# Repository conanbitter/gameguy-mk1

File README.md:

# GameGuy mk1
Simple portable game console. Based on ATMega328P.

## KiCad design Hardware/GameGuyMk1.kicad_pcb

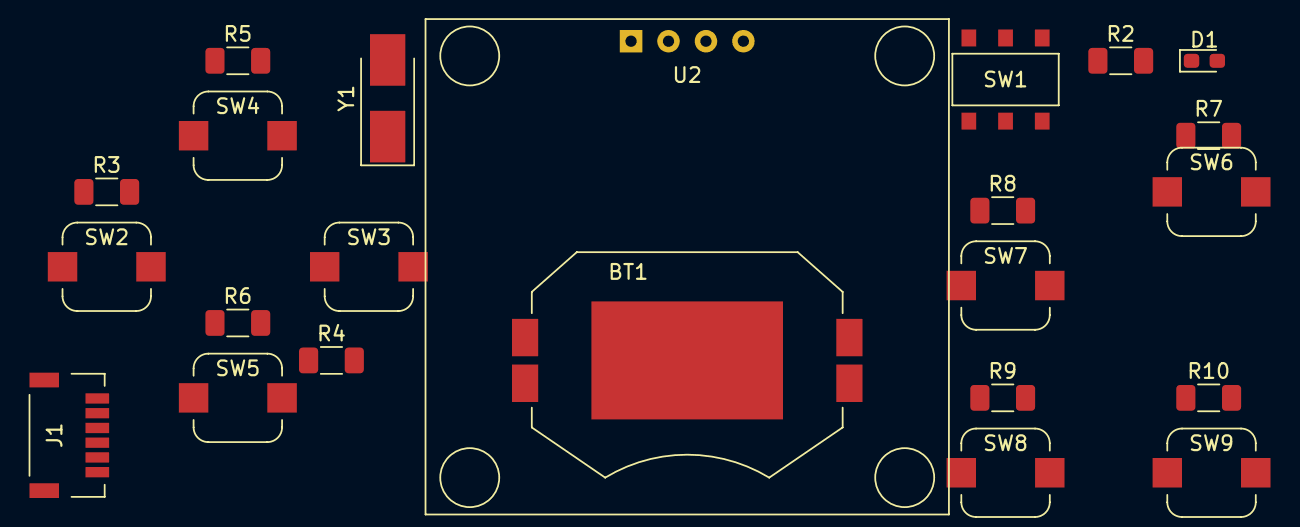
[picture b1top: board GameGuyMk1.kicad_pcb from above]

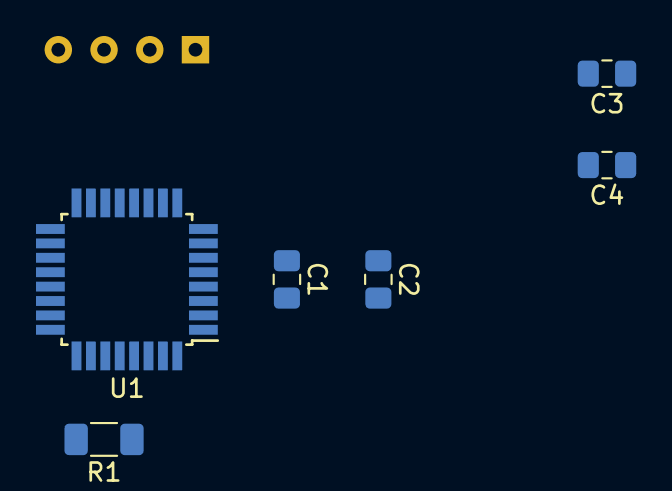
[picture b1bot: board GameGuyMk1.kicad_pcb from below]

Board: 2 copper layers, 29 parts (6 on the bottom side), 21 nets, no tracks yet.

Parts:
BT1: 3V; Battery_Holder
C1, C2: 0.1uF; C_0805_2012Metric_Pad1.18x1.45mm_HandSolder
C3, C4: 22pF; C_0805_2012Metric_Pad1.18x1.45mm_HandSolder
D1: LED; LED_0603_1608Metric_Pad1.05x0.95mm_HandSolder
J1: AVR-ISP-6; Connector_JST1.0_6pin
R1, R3, R4, R5, R6, R7, R8, R9, R10: 10k; R_1206_3216Metric_Pad1.30x1.75mm_HandSolder
R2: 330; R_1206_3216Metric_Pad1.30x1.75mm_HandSolder
SW1: POWER; AYZ0202
SW2: Left; Silent_Button
SW3: Right; Silent_Button
SW4: Up; Silent_Button
SW5: Down; Silent_Button
SW6: Btn_A; Silent_Button
SW7: Btn_B; Silent_Button
SW8: Play; Silent_Button
SW9: Esc; Silent_Button
U1: ATmega328P-AU; TQFP-32_7x7mm_P0.8mm
U2: OLED_I2C; OLED_1.3inch_128x64
Y1: 8MHz; Crystal_SMD_5032-2Pin_5.0x3.2mm_HandSoldering

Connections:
+3V0: C1.2, C2.1, J1.2, R1.2, R2.2, R3.1, R4.1, R5.1, R6.1, R7.1, R8.1, R9.1, R10.1, SW1.3, U1.4, U1.6, U1.18, U1.20, U2.1
BTN-A: R7.2, SW6.1, U1.2
BTN-B: R8.2, SW7.1, U1.9
BTN-DOWN: R6.2, SW5.1, U1.1
BTN-ESC: R10.2, SW9.1, U1.11
BTN-LEFT: R3.2, SW2.1, U1.30
BTN-PLAY: R9.2, SW8.1, U1.10
BTN-RIGHT: R4.2, SW3.1, U1.31
BTN-UP: R5.2, SW4.1, U1.32
GND: BT1.2, C1.1, C2.2, C3.1, C4.1, J1.6, SW2.2, SW3.2, SW4.2, SW5.2, SW6.2, SW7.2, SW8.2, SW9.2, U1.3, U1.5, U1.21, U2.2
I2C-SCL: U1.28, U2.3
I2C-SDA: U1.27, U2.4
ISP-MISO: J1.1, U1.16
ISP-MOSI: J1.4, U1.15
ISP-RST: J1.5, R1.1, U1.29
ISP-SCK: J1.3, U1.17
unnamed: BT1.1, SW1.2
unnamed: C3.2, U1.7, Y1.1
unnamed: C4.2, U1.8, Y1.2
unnamed: D1.1, U1.12
unnamed: D1.2, R2.1

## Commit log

2021-08-15 Corrected totle of the Readme
2021-08-15 Added KiCad schema
2021-08-15 Added all symbols to schematic
2021-08-15 Finished schematics
2021-08-15 Added annotations a nd footprints
2021-08-15 Improvements, added power switch and buttons
2021-08-15 Added I2C bus
2021-08-15 Making own footprints
2021-08-15 Added OLED display
2021-08-15 Added JSP 6 pin connector for ISP
2021-08-15 Added Battery Holder
2021-08-15 Added power switch
2021-08-15 Updated footprints
2021-08-15 Added symbol for display
2021-08-15 Updated footprint for screen
2021-08-15 Removed big decoupling capacitor
2021-08-15 Draft of pcb
2021-08-15 Footprints updated for hand soldering
